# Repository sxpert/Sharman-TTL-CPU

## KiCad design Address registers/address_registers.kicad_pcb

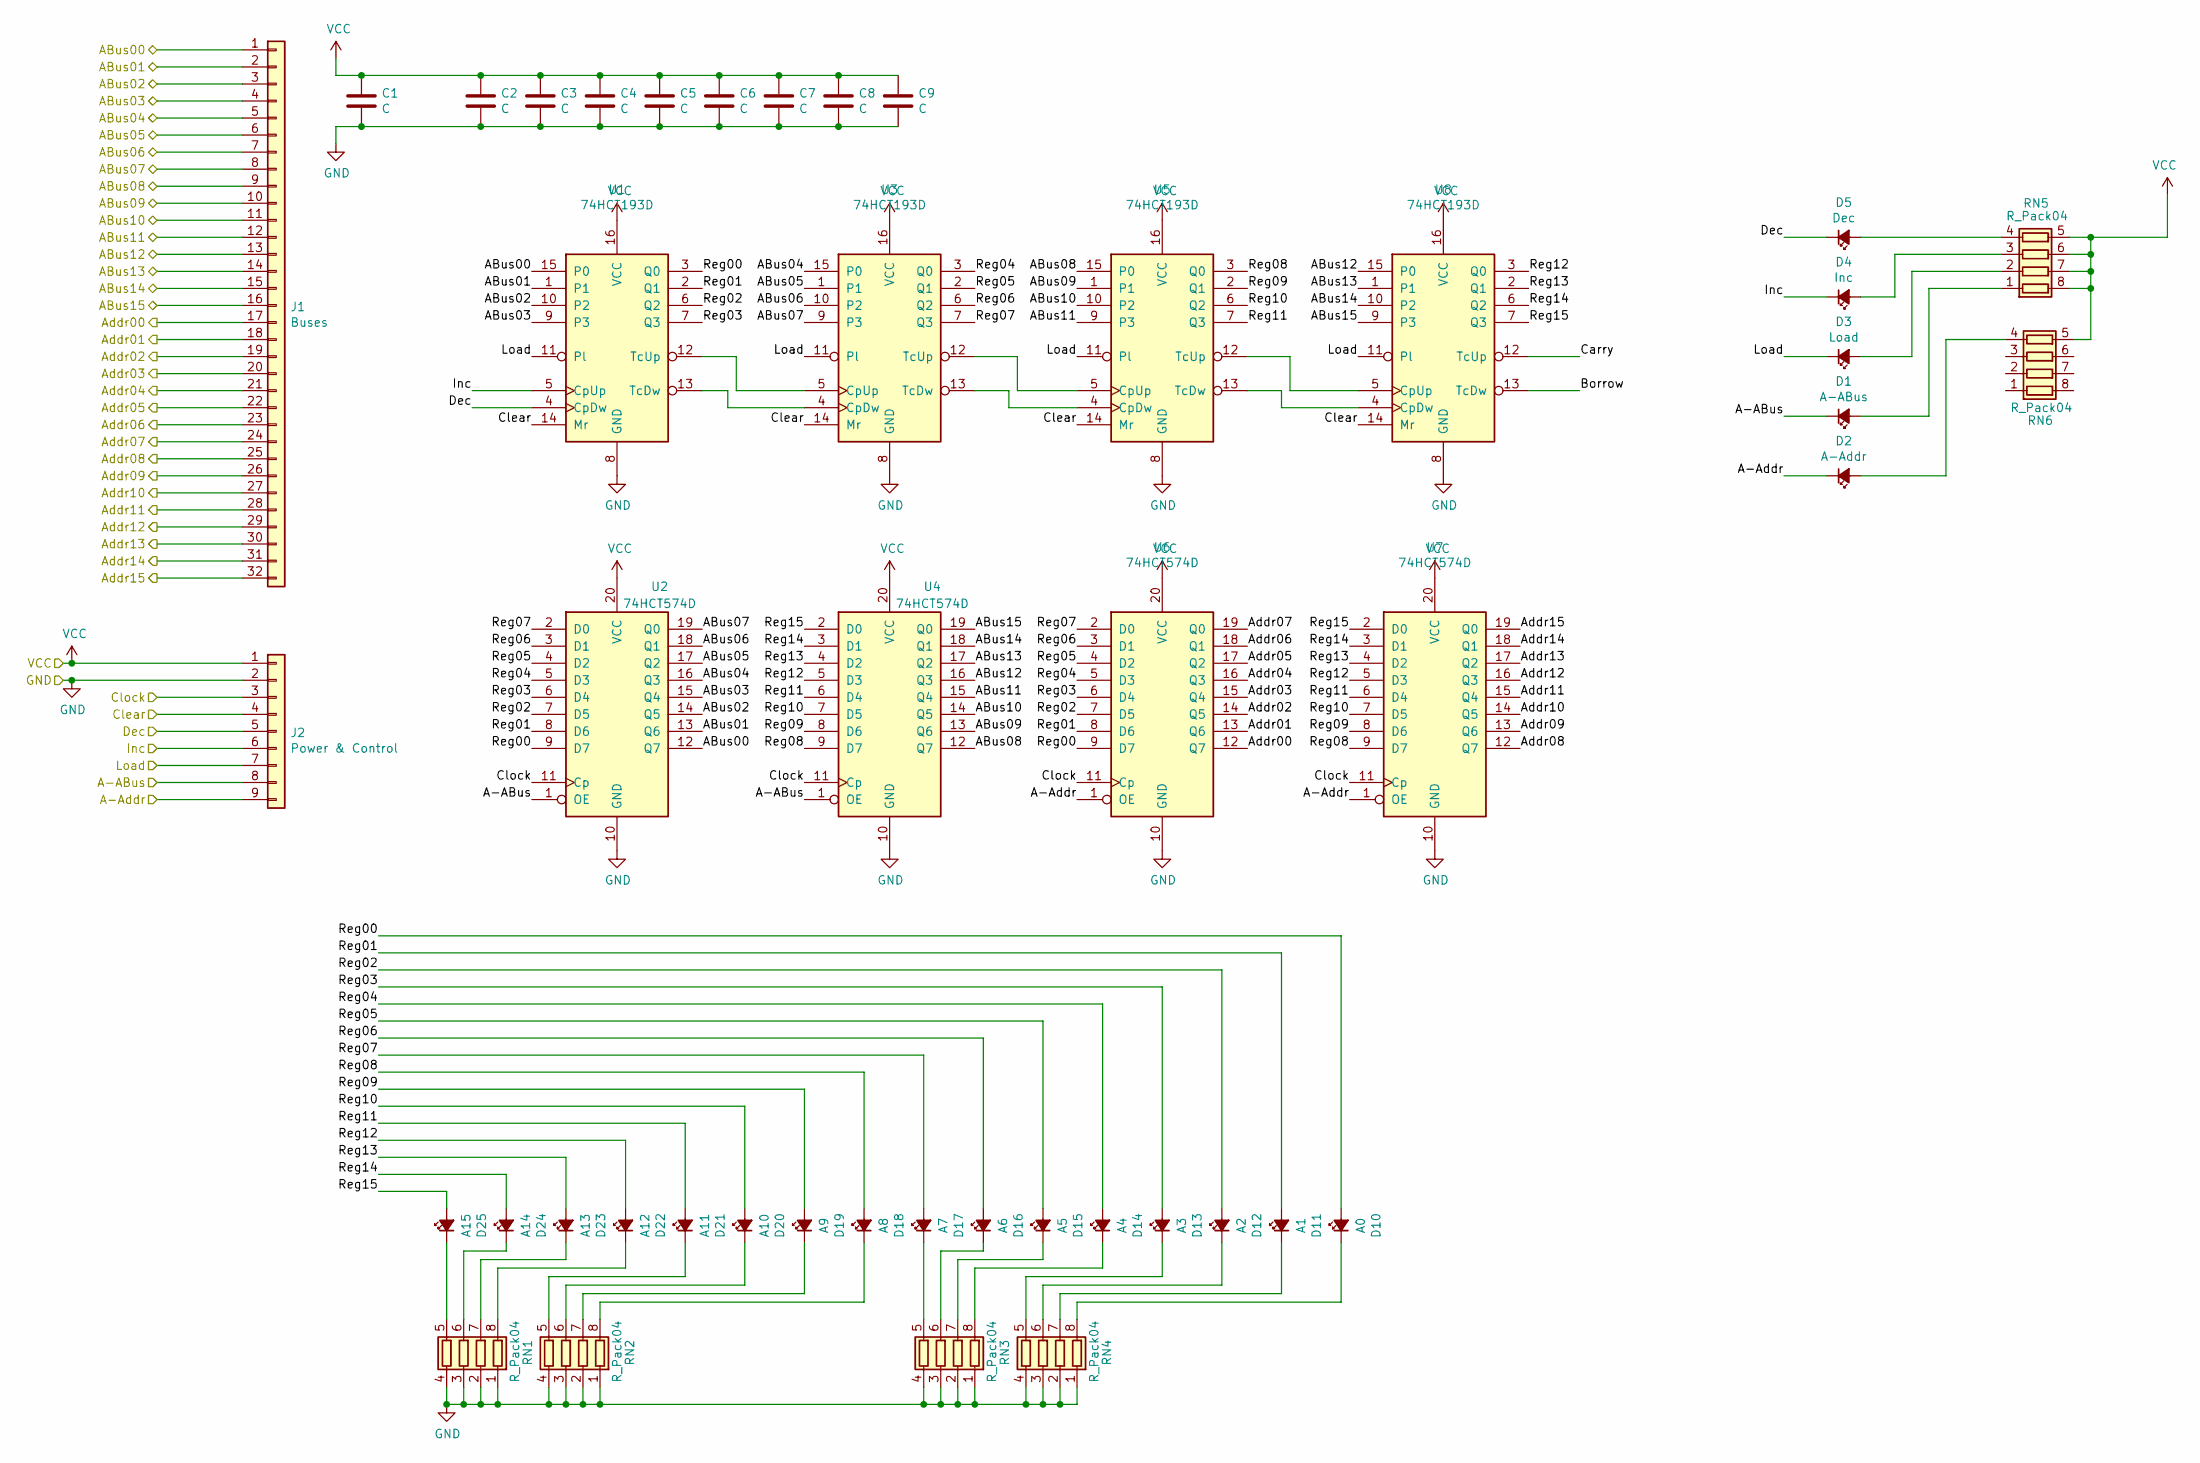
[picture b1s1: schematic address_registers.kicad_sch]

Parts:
C1, C2, C3, C4, C5, C6, C7, C8, C9: C; C_1206_3216Metric
D1: A-ABus; LED_1206_3216Metric
D2: A-Addr; LED_1206_3216Metric
D3: Load; LED_1206_3216Metric
D4: Inc; LED_1206_3216Metric
D5: Dec; LED_1206_3216Metric
D10: A0; LED_1206_3216Metric
D11: A1; LED_1206_3216Metric
D12: A2; LED_1206_3216Metric
D13: A3; LED_1206_3216Metric
D14: A4; LED_1206_3216Metric
D15: A5; LED_1206_3216Metric
D16: A6; LED_1206_3216Metric
D17: A7; LED_1206_3216Metric
D18: A8; LED_1206_3216Metric
D19: A9; LED_1206_3216Metric
D20: A10; LED_1206_3216Metric
D21: A11; LED_1206_3216Metric
D22: A12; LED_1206_3216Metric
D23: A13; LED_1206_3216Metric
D24: A14; LED_1206_3216Metric
D25: A15; LED_1206_3216Metric
J1: Buses; PinHeader_1x32_P2.54mm_Vertical
J2: Power & Control; PinHeader_1x09_P2.54mm_Vertical
RN1, RN2, RN3, RN4, RN5, RN6: R_Pack04; R_Array_Convex_4x1206
U1, U3, U5, U8: 74HCT193D; SOIC-16_3.9x9.9mm_P1.27mm
U2, U4, U6, U7: 74HCT574D; SOIC-20W_7.5x12.8mm_P1.27mm

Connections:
/A-ABus: D1.1 (K), J2.8, U2.1 (OE), U4.1 (OE)
/A-Addr: D2.1 (K), J2.9, U6.1 (OE), U7.1 (OE)
/ABus00: J1.1, U1.15 (P0), U2.12 (Q7)
/ABus01: J1.2, U1.1, U2.13 (Q6)
/ABus02: J1.3, U1.10 (P2), U2.14 (Q5)
/ABus03: J1.4, U1.9 (P3), U2.15 (Q4)
/ABus04: J1.5, U2.16 (Q3), U3.15 (P0)
/ABus05: J1.6, U2.17 (Q2), U3.1
/ABus06: J1.7, U2.18 (Q1), U3.10 (P2)
/ABus07: J1.8, U2.19 (Q0), U3.9 (P3)
/ABus08: J1.9, U4.12 (Q7), U5.15 (P0)
/ABus09: J1.10, U4.13 (Q6), U5.1
/ABus10: J1.11, U4.14 (Q5), U5.10 (P2)
/ABus11: J1.12, U4.15 (Q4), U5.9 (P3)
/ABus12: J1.13, U4.16 (Q3), U8.15 (P0)
/ABus13: J1.14, U4.17 (Q2), U8.1
/ABus14: J1.15, U4.18 (Q1), U8.10 (P2)
/ABus15: J1.16, U4.19 (Q0), U8.9 (P3)
/Addr00: J1.17, U6.12 (Q7)
/Addr01: J1.18, U6.13 (Q6)
/Addr02: J1.19, U6.14 (Q5)
/Addr03: J1.20, U6.15 (Q4)
/Addr04: J1.21, U6.16 (Q3)
/Addr05: J1.22, U6.17 (Q2)
/Addr06: J1.23, U6.18 (Q1)
/Addr07: J1.24, U6.19 (Q0)
/Addr08: J1.25, U7.12 (Q7)
/Addr09: J1.26, U7.13 (Q6)
/Addr10: J1.27, U7.14 (Q5)
/Addr11: J1.28, U7.15 (Q4)
/Addr12: J1.29, U7.16 (Q3)
/Addr13: J1.30, U7.17 (Q2)
/Addr14: J1.31, U7.18 (Q1)
/Addr15: J1.32, U7.19 (Q0)
/Borrow: U8.13 (TcDw)
/Carry: U8.12 (TcUp)
/Clear: J2.4, U1.14 (Mr), U3.14 (Mr), U5.14 (Mr), U8.14 (Mr)
/Clock: J2.3, U2.11 (Cp), U4.11 (Cp), U6.11 (Cp), U7.11 (Cp)
/Dec: D5.1 (K), J2.5, U1.4 (CpDw)
/Inc: D4.1 (K), J2.6, U1.5 (CpUp)
/Load: D3.1 (K), J2.7, U1.11 (Pl), U3.11 (Pl), U5.11 (Pl), U8.11 (Pl)
/Reg00: D10.2 (A), U1.3 (Q0), U2.9 (D7), U6.9 (D7)
/Reg01: D11.2 (A), U1.2 (Q1), U2.8 (D6), U6.8 (D6)
/Reg02: D12.2 (A), U1.6 (Q2), U2.7 (D5), U6.7 (D5)
/Reg03: D13.2 (A), U1.7 (Q3), U2.6 (D4), U6.6 (D4)
/Reg04: D14.2 (A), U2.5 (D3), U3.3 (Q0), U6.5 (D3)
/Reg05: D15.2 (A), U2.4 (D2), U3.2 (Q1), U6.4 (D2)
/Reg06: D16.2 (A), U2.3 (D1), U3.6 (Q2), U6.3 (D1)
/Reg07: D17.2 (A), U2.2 (D0), U3.7 (Q3), U6.2 (D0)
/Reg08: D18.2 (A), U4.9 (D7), U5.3 (Q0), U7.9 (D7)
/Reg09: D19.2 (A), U4.8 (D6), U5.2 (Q1), U7.8 (D6)
/Reg10: D20.2 (A), U4.7 (D5), U5.6 (Q2), U7.7 (D5)
/Reg11: D21.2 (A), U4.6 (D4), U5.7 (Q3), U7.6 (D4)
/Reg12: D22.2 (A), U4.5 (D3), U7.5 (D3), U8.3 (Q0)
/Reg13: D23.2 (A), U4.4 (D2), U7.4 (D2), U8.2 (Q1)
/Reg14: D24.2 (A), U4.3 (D1), U7.3 (D1), U8.6 (Q2)
/Reg15: D25.2 (A), U4.2 (D0), U7.2 (D0), U8.7 (Q3)
GND: C1.2, C2.2, C3.2, C4.2, C5.2, C6.2, C7.2, C8.2, C9.2, J2.2, RN1.1 (R1.1), RN1.2 (R2.1), RN1.3 (R3.1), RN1.4 (R4.1), RN2.1 (R1.1), RN2.2 (R2.1), RN2.3 (R3.1), RN2.4 (R4.1), RN3.1 (R1.1), RN3.2 (R2.1), RN3.3 (R3.1), RN3.4 (R4.1), RN4.1 (R1.1), RN4.2 (R2.1), RN4.3 (R3.1), RN4.4 (R4.1), U1.8 (GND), U2.10 (GND), U3.8 (GND), U4.10 (GND), U5.8 (GND), U6.10 (GND), U7.10 (GND), U8.8 (GND)
unnamed: D1.2 (A), RN5.1 (R1.1)
unnamed: D2.2 (A), RN6.4 (R4.1)
unnamed: D3.2 (A), RN5.2 (R2.1)
unnamed: D4.2 (A), RN5.3 (R3.1)
unnamed: D5.2 (A), RN5.4 (R4.1)
unnamed: D10.1 (K), RN4.8 (R1.2)
unnamed: D11.1 (K), RN4.7 (R2.2)
unnamed: D12.1 (K), RN4.6 (R3.2)
unnamed: D13.1 (K), RN4.5 (R4.2)
unnamed: D14.1 (K), RN3.8 (R1.2)
unnamed: D15.1 (K), RN3.7 (R2.2)
unnamed: D16.1 (K), RN3.6 (R3.2)
unnamed: D17.1 (K), RN3.5 (R4.2)
unnamed: D18.1 (K), RN2.8 (R1.2)
unnamed: D19.1 (K), RN2.7 (R2.2)
unnamed: D20.1 (K), RN2.6 (R3.2)
unnamed: D21.1 (K), RN2.5 (R4.2)
unnamed: D22.1 (K), RN1.8 (R1.2)
unnamed: D23.1 (K), RN1.7 (R2.2)
unnamed: D24.1 (K), RN1.6 (R3.2)
unnamed: D25.1 (K), RN1.5 (R4.2)
unnamed: U1.12 (TcUp), U3.5 (CpUp)
unnamed: U1.13 (TcDw), U3.4 (CpDw)
unnamed: U3.12 (TcUp), U5.5 (CpUp)
unnamed: U3.13 (TcDw), U5.4 (CpDw)
unnamed: U5.12 (TcUp), U8.5 (CpUp)
unnamed: U5.13 (TcDw), U8.4 (CpDw)
VCC: C1.1, C2.1, C3.1, C4.1, C5.1, C6.1, C7.1, C8.1, C9.1, J2.1, RN5.5 (R4.2), RN5.6 (R3.2), RN5.7 (R2.2), RN5.8 (R1.2), RN6.5 (R4.2), U1.16 (VCC), U2.20 (VCC), U3.16 (VCC), U4.20 (VCC), U5.16 (VCC), U6.20 (VCC), U7.20 (VCC), U8.16 (VCC)

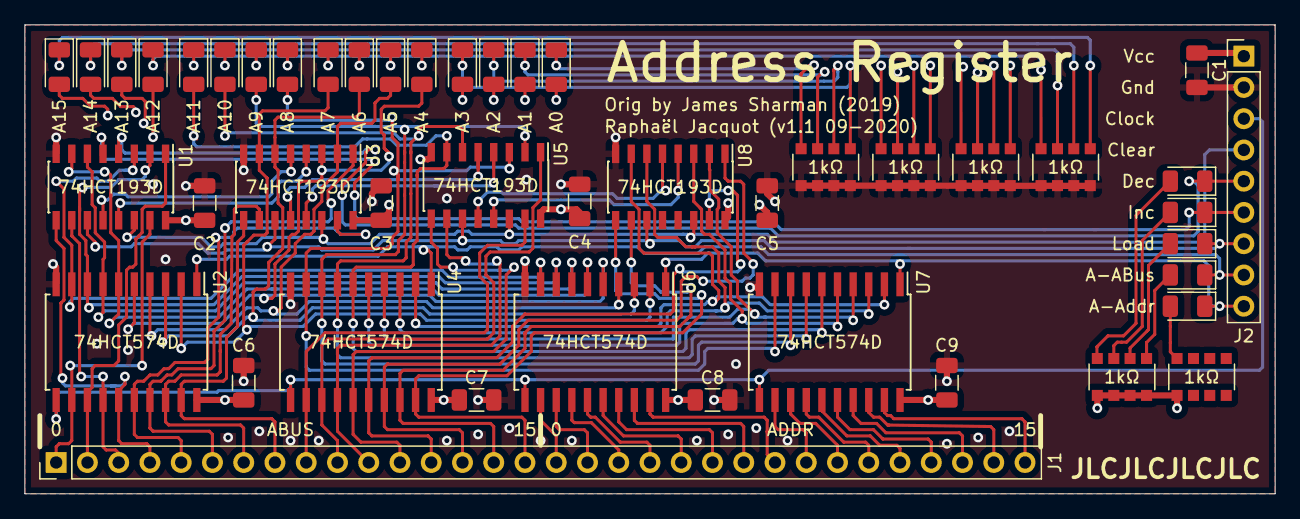
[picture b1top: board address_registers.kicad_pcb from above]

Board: 4 copper layers, 101.6 x 38.1 mm, 46 parts (0 on the bottom side), 84 nets.

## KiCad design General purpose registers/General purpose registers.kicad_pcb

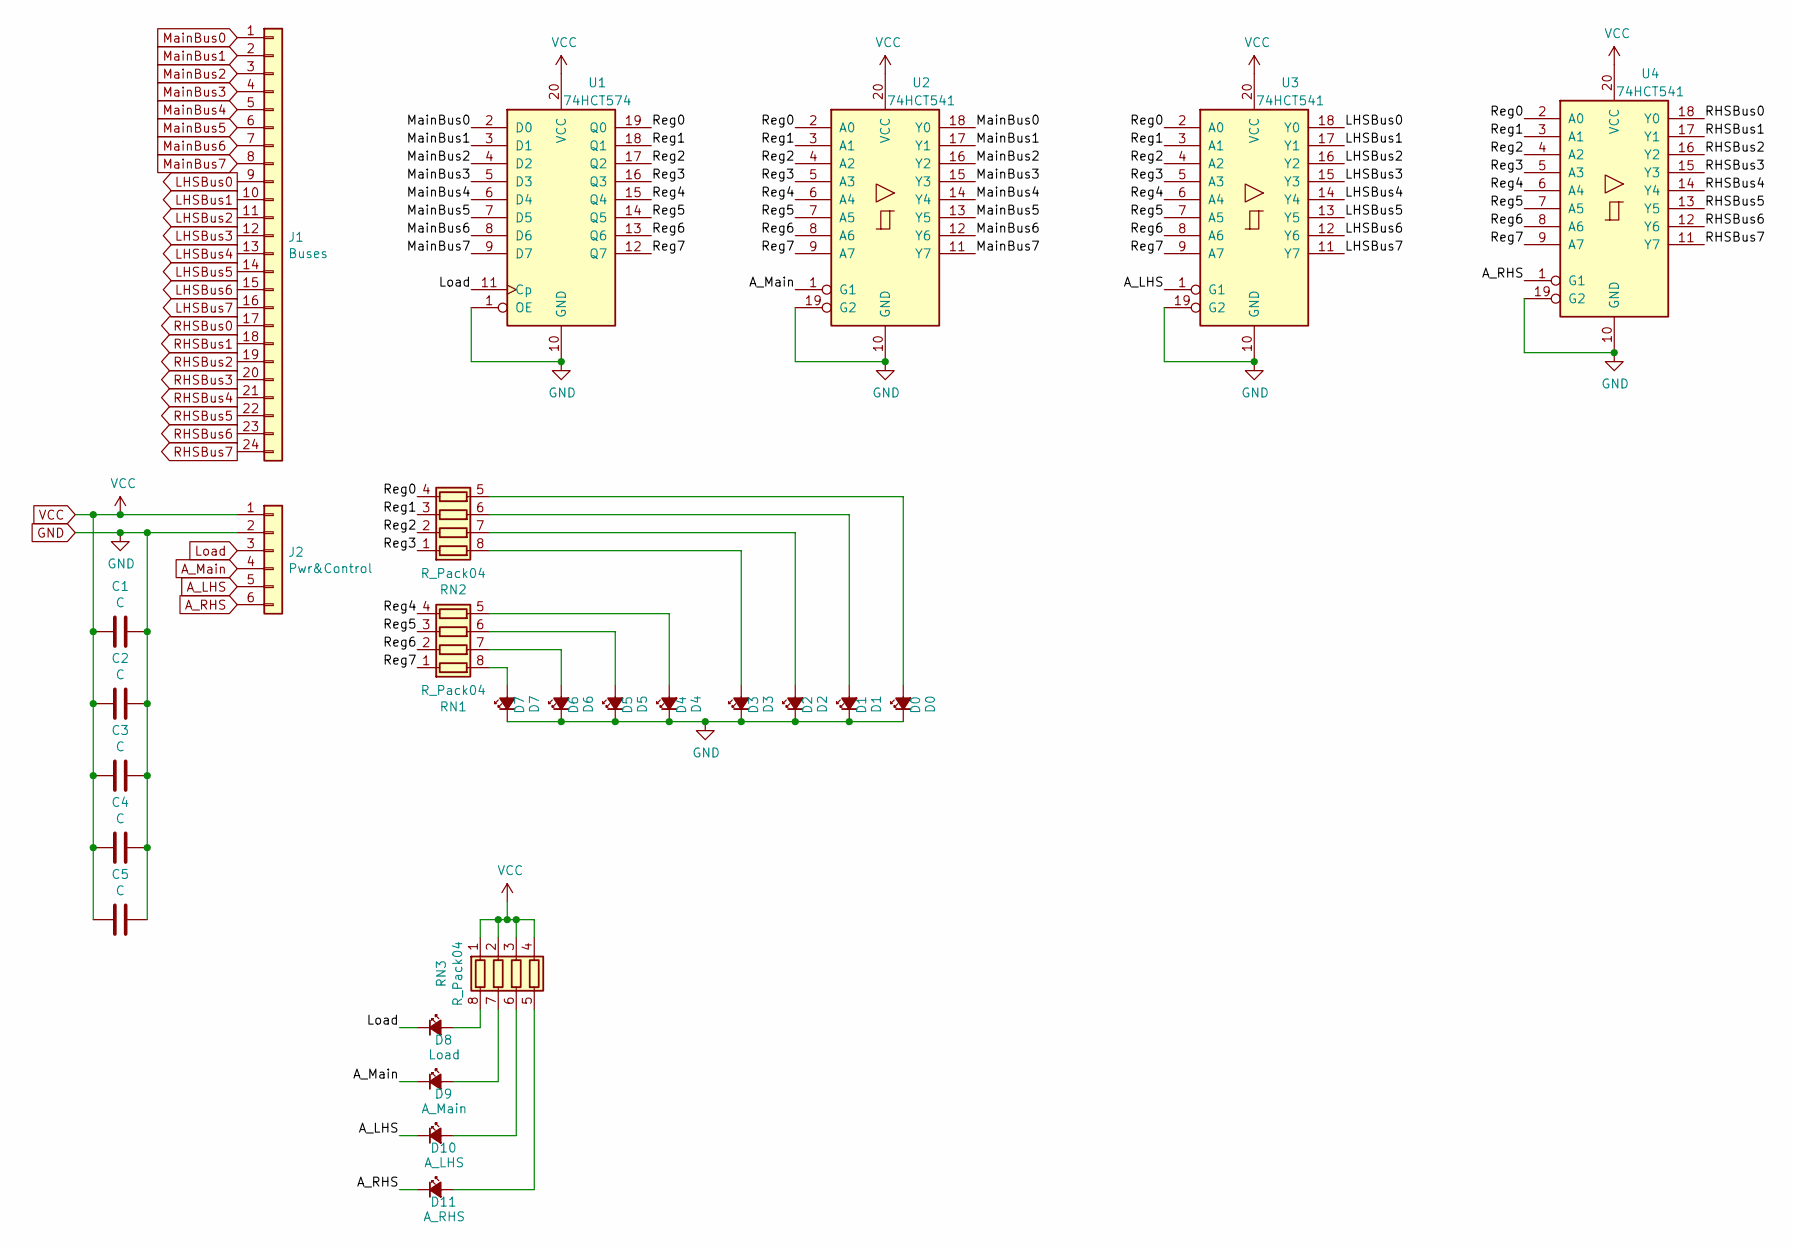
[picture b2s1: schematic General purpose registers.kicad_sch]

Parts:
C1, C2, C3, C4, C5: C; C_1206_3216Metric
D0: D0; LED_1206_3216Metric
D1: D1; LED_1206_3216Metric
D2: D2; LED_1206_3216Metric
D3: D3; LED_1206_3216Metric
D4: D4; LED_1206_3216Metric
D5: D5; LED_1206_3216Metric
D6: D6; LED_1206_3216Metric
D7: D7; LED_1206_3216Metric
D8: Load; LED_1206_3216Metric
D9: A_Main; LED_1206_3216Metric
D10: A_LHS; LED_1206_3216Metric
D11: A_RHS; LED_1206_3216Metric
J1: Buses; PinHeader_1x24_P2.54mm_Vertical
J2: Pwr&Control; PinHeader_1x06_P2.54mm_Vertical
RN1, RN2, RN3: R_Pack04; R_Array_Convex_4x1206
U1: 74HCT574; SOIC-20W_7.5x12.8mm_P1.27mm
U2, U3, U4: 74HCT541; SOIC-20W_7.5x12.8mm_P1.27mm

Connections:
/Reg0: RN2.4 (R4.1), U1.19 (Q0), U2.2 (A0), U3.2 (A0), U4.2 (A0)
/Reg1: RN2.3 (R3.1), U1.18 (Q1), U2.3 (A1), U3.3 (A1), U4.3 (A1)
/Reg2: RN2.2 (R2.1), U1.17 (Q2), U2.4 (A2), U3.4 (A2), U4.4 (A2)
/Reg3: RN2.1 (R1.1), U1.16 (Q3), U2.5 (A3), U3.5 (A3), U4.5 (A3)
/Reg4: RN1.4 (R4.1), U1.15 (Q4), U2.6 (A4), U3.6 (A4), U4.6 (A4)
/Reg5: RN1.3 (R3.1), U1.14 (Q5), U2.7 (A5), U3.7 (A5), U4.7 (A5)
/Reg6: RN1.2 (R2.1), U1.13 (Q6), U2.8 (A6), U3.8 (A6), U4.8 (A6)
/Reg7: RN1.1 (R1.1), U1.12 (Q7), U2.9 (A7), U3.9 (A7), U4.9 (A7)
A_LHS: D10.1 (K), J2.5, U3.1 (G1)
A_Main: D9.1 (K), J2.4, U2.1 (G1)
A_RHS: D11.1 (K), J2.6, U4.1 (G1)
GND: C1.1, C2.1, C3.1, C4.1, C5.1, D0.1 (K), D1.1 (K), D2.1 (K), D3.1 (K), D4.1 (K), D5.1 (K), D6.1 (K), D7.1 (K), J2.2, U1.1 (OE), U1.10 (GND), U2.10 (GND), U2.19 (G2), U3.10 (GND), U3.19 (G2), U4.10 (GND), U4.19 (G2)
LHSBus0: J1.9, U3.18 (Y0)
LHSBus1: J1.10, U3.17 (Y1)
LHSBus2: J1.11, U3.16 (Y2)
LHSBus3: J1.12, U3.15 (Y3)
LHSBus4: J1.13, U3.14 (Y4)
LHSBus5: J1.14, U3.13 (Y5)
LHSBus6: J1.15, U3.12 (Y6)
LHSBus7: J1.16, U3.11 (Y7)
Load: D8.1 (K), J2.3, U1.11 (Cp)
MainBus0: J1.1, U1.2 (D0), U2.18 (Y0)
MainBus1: J1.2, U1.3 (D1), U2.17 (Y1)
MainBus2: J1.3, U1.4 (D2), U2.16 (Y2)
MainBus3: J1.4, U1.5 (D3), U2.15 (Y3)
MainBus4: J1.5, U1.6 (D4), U2.14 (Y4)
MainBus5: J1.6, U1.7 (D5), U2.13 (Y5)
MainBus6: J1.7, U1.8 (D6), U2.12 (Y6)
MainBus7: J1.8, U1.9 (D7), U2.11 (Y7)
unnamed: D0.2 (A), RN2.5 (R4.2)
unnamed: D1.2 (A), RN2.6 (R3.2)
unnamed: D2.2 (A), RN2.7 (R2.2)
unnamed: D3.2 (A), RN2.8 (R1.2)
unnamed: D4.2 (A), RN1.5 (R4.2)
unnamed: D5.2 (A), RN1.6 (R3.2)
unnamed: D6.2 (A), RN1.7 (R2.2)
unnamed: D7.2 (A), RN1.8 (R1.2)
unnamed: D8.2 (A), RN3.8 (R1.2)
unnamed: D9.2 (A), RN3.7 (R2.2)
unnamed: D10.2 (A), RN3.6 (R3.2)
unnamed: D11.2 (A), RN3.5 (R4.2)
RHSBus0: J1.17, U4.18 (Y0)
RHSBus1: J1.18, U4.17 (Y1)
RHSBus2: J1.19, U4.16 (Y2)
RHSBus3: J1.20, U4.15 (Y3)
RHSBus4: J1.21, U4.14 (Y4)
RHSBus5: J1.22, U4.13 (Y5)
RHSBus6: J1.23, U4.12 (Y6)
RHSBus7: J1.24, U4.11 (Y7)
VCC: C1.2, C2.2, C3.2, C4.2, C5.2, J2.1, RN3.1 (R1.1), RN3.2 (R2.1), RN3.3 (R3.1), RN3.4 (R4.1), U1.20 (VCC), U2.20 (VCC), U3.20 (VCC), U4.20 (VCC)

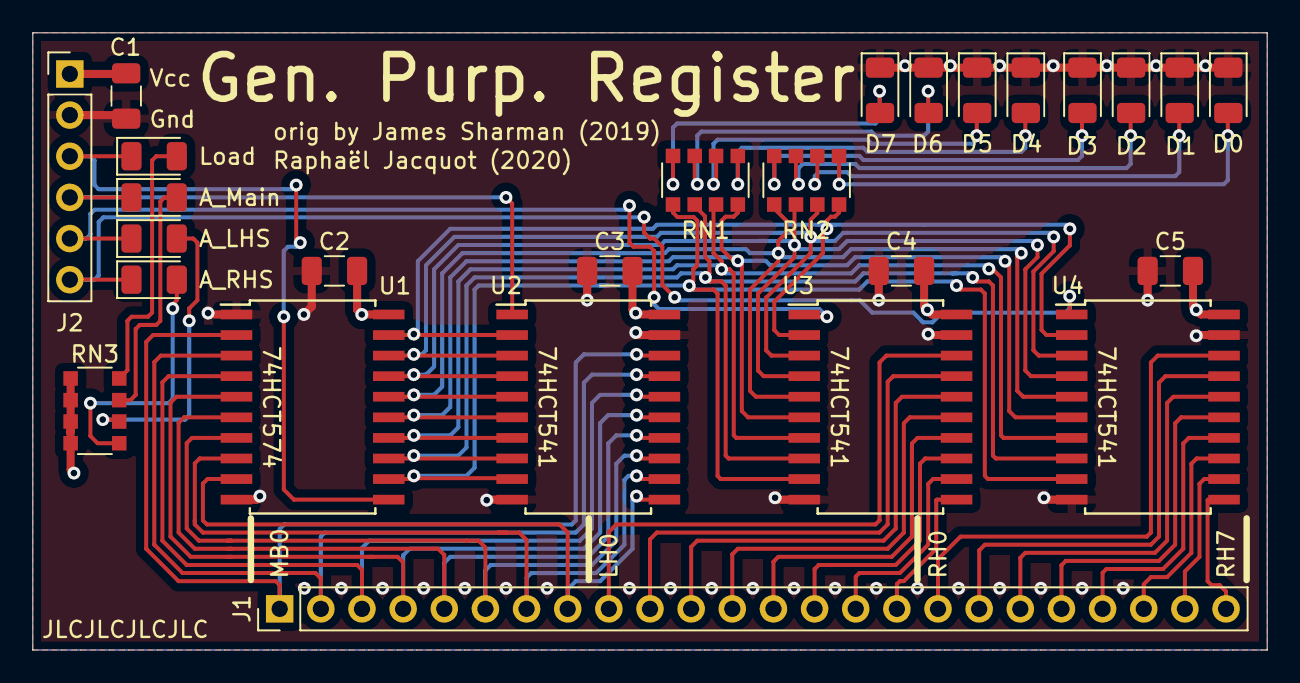
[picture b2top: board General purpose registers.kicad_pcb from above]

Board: 4 copper layers, 76.2 x 38.1 mm, 26 parts (0 on the bottom side), 50 nets.

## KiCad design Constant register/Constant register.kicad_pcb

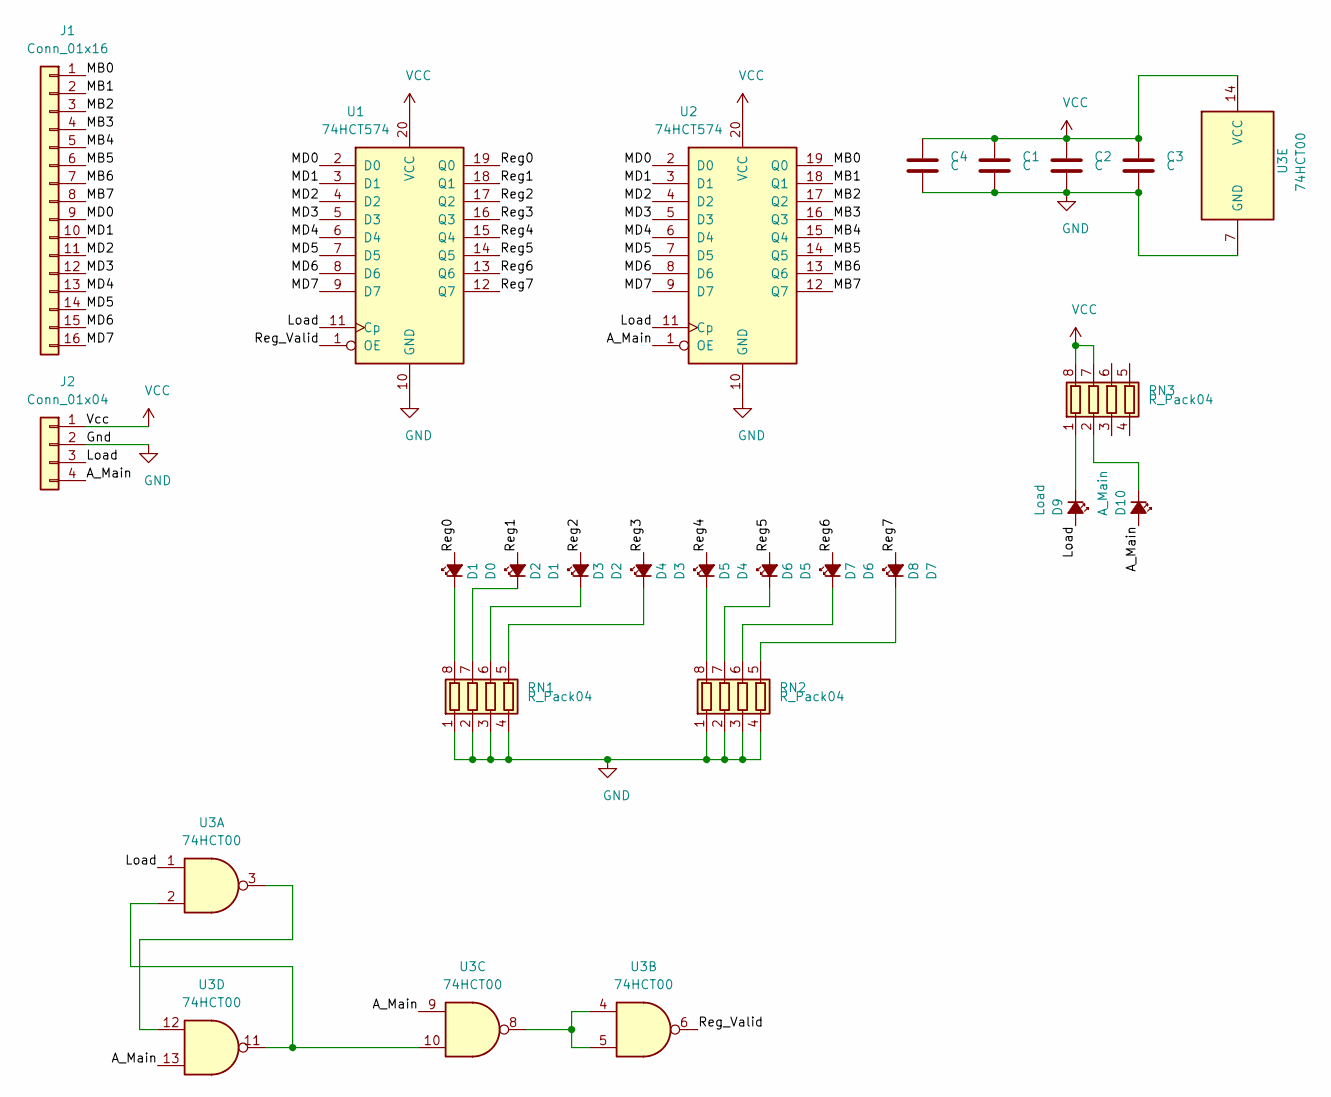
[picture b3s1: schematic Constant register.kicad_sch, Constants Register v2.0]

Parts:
C1, C2, C3, C4: C; C_1206_3216Metric
D1: D0; LED_1206_3216Metric
D2: D1; LED_1206_3216Metric
D3: D2; LED_1206_3216Metric
D4: D3; LED_1206_3216Metric
D5: D4; LED_1206_3216Metric
D6: D5; LED_1206_3216Metric
D7: D6; LED_1206_3216Metric
D8: D7; LED_1206_3216Metric
D9: Load; LED_1206_3216Metric
D10: A_Main; LED_1206_3216Metric
J1: Conn_01x16; PinHeader_1x16_P2.54mm_Vertical
J2: Conn_01x04; PinHeader_1x04_P2.54mm_Vertical
RN1, RN2, RN3: R_Pack04; R_Array_Convex_4x1206
U1, U2: 74HCT574; SOIC-20W_7.5x12.8mm_P1.27mm
U3: 74HCT00; SOIC-14_3.9x8.7mm_P1.27mm

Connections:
/A_Main: D10.2 (A), J2.4, U2.1 (OE), U3.9, U3.13
/Load: D9.2 (A), J2.3, U1.11 (Cp), U2.11 (Cp), U3.1
/MB0: J1.1, U2.19 (Q0)
/MB1: J1.2, U2.18 (Q1)
/MB2: J1.3, U2.17 (Q2)
/MB3: J1.4, U2.16 (Q3)
/MB4: J1.5, U2.15 (Q4)
/MB5: J1.6, U2.14 (Q5)
/MB6: J1.7, U2.13 (Q6)
/MB7: J1.8, U2.12 (Q7)
/MD0: J1.9, U1.2 (D0), U2.2 (D0)
/MD1: J1.10, U1.3 (D1), U2.3 (D1)
/MD2: J1.11, U1.4 (D2), U2.4 (D2)
/MD3: J1.12, U1.5 (D3), U2.5 (D3)
/MD4: J1.13, U1.6 (D4), U2.6 (D4)
/MD5: J1.14, U1.7 (D5), U2.7 (D5)
/MD6: J1.15, U1.8 (D6), U2.8 (D6)
/MD7: J1.16, U1.9 (D7), U2.9 (D7)
/Reg0: D1.2 (A), U1.19 (Q0)
/Reg1: D2.2 (A), U1.18 (Q1)
/Reg2: D3.2 (A), U1.17 (Q2)
/Reg3: D4.2 (A), U1.16 (Q3)
/Reg4: D5.2 (A), U1.15 (Q4)
/Reg5: D6.2 (A), U1.14 (Q5)
/Reg6: D7.2 (A), U1.13 (Q6)
/Reg7: D8.2 (A), U1.12 (Q7)
/Reg_Valid: U1.1 (OE), U3.6
GND: C1.2, C2.2, C3.2, C4.2, J2.2, RN1.1 (R1.1), RN1.2 (R2.1), RN1.3 (R3.1), RN1.4 (R4.1), RN2.1 (R1.1), RN2.2 (R2.1), RN2.3 (R3.1), RN2.4 (R4.1), U1.10 (GND), U2.10 (GND), U3.7 (GND)
unnamed: D1.1 (K), RN1.8 (R1.2)
unnamed: D2.1 (K), RN1.7 (R2.2)
unnamed: D3.1 (K), RN1.6 (R3.2)
unnamed: D4.1 (K), RN1.5 (R4.2)
unnamed: D5.1 (K), RN2.8 (R1.2)
unnamed: D6.1 (K), RN2.7 (R2.2)
unnamed: D7.1 (K), RN2.6 (R3.2)
unnamed: D8.1 (K), RN2.5 (R4.2)
unnamed: D9.1 (K), RN3.1 (R1.1)
unnamed: D10.1 (K), RN3.2 (R2.1)
unnamed: U3.4, U3.5, U3.8
unnamed: U3.2, U3.10, U3.11
unnamed: U3.3, U3.12
VCC: C1.1, C2.1, C3.1, C4.1, J2.1, RN3.7 (R2.2), RN3.8 (R1.2), U1.20 (VCC), U2.20 (VCC), U3.14 (VCC)

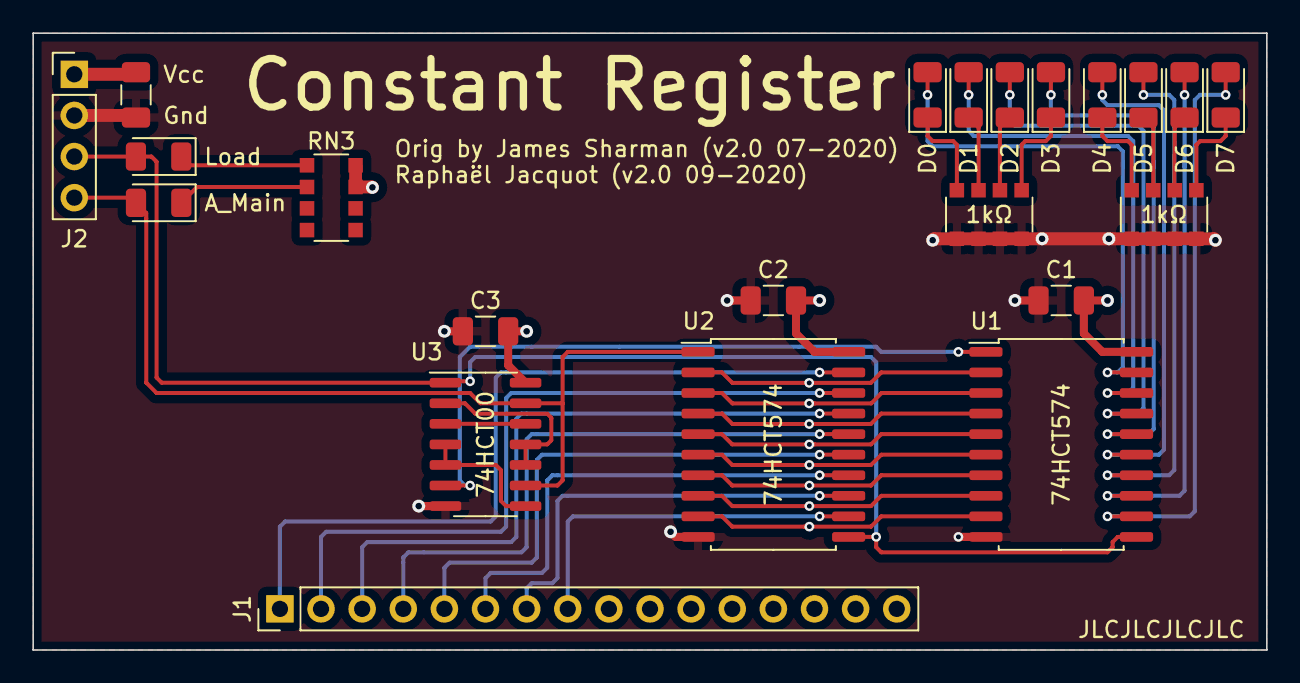
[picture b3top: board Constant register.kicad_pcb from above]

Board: 4 copper layers, 76.2 x 38.1 mm, 22 parts (0 on the bottom side), 42 nets.

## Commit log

2020-09-10 add Address Register
2020-09-10 added modules library
2020-09-10 added Constant Register
2020-09-10 added General Purpose Register
2020-09-10 added the Motherboard
2020-09-10 move to Constant Register v2.0
2020-09-10 general cleanup
